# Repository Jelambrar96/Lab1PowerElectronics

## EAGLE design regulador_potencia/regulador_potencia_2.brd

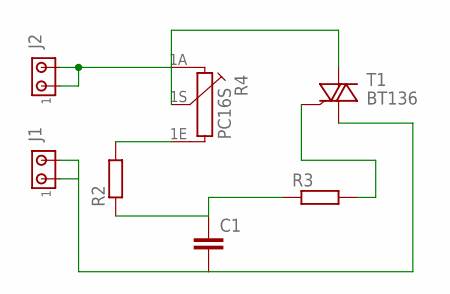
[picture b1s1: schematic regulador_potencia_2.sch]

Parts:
C1: C2.5/5; C2.5-5
J1, J2: MTA02-156; 1X2MTA
R2, R3: R-EU_0207/12; 0207/12
R4: PC16S
T1: BT136; TO220AB

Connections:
unnamed: R2.2, R4.1E
unnamed: J2.1, J2.2, R4.1A, R4.1S, T1.2 (A2)
unnamed: C1.2, J1.1, J1.2, T1.1 (A1)
unnamed: C1.1, R2.1, R3.1
unnamed: R3.2, T1.3 (G)

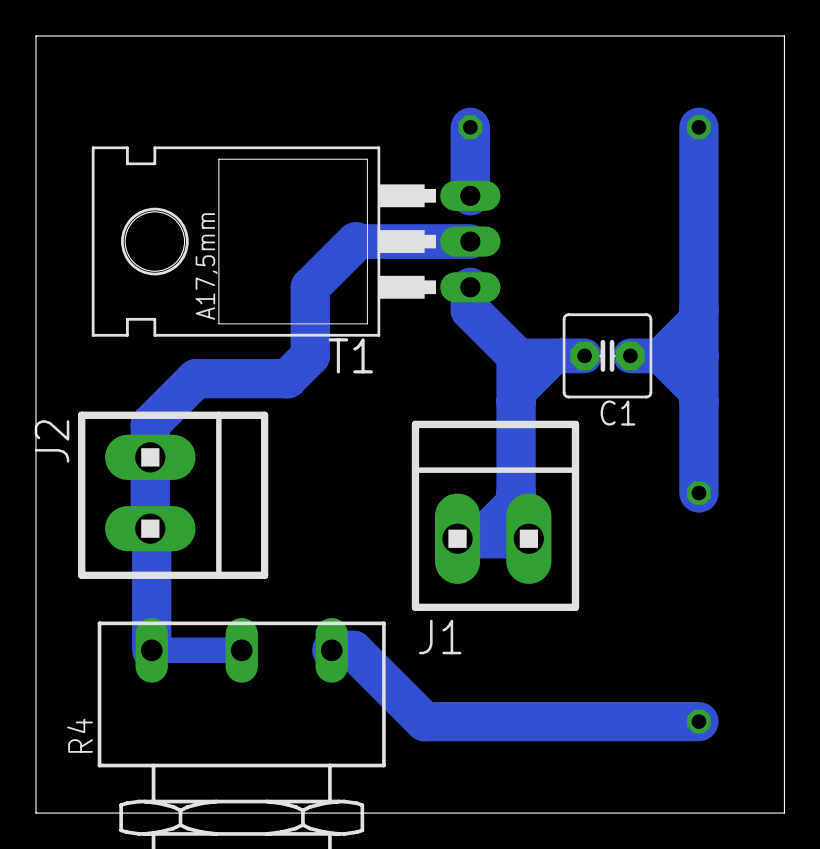
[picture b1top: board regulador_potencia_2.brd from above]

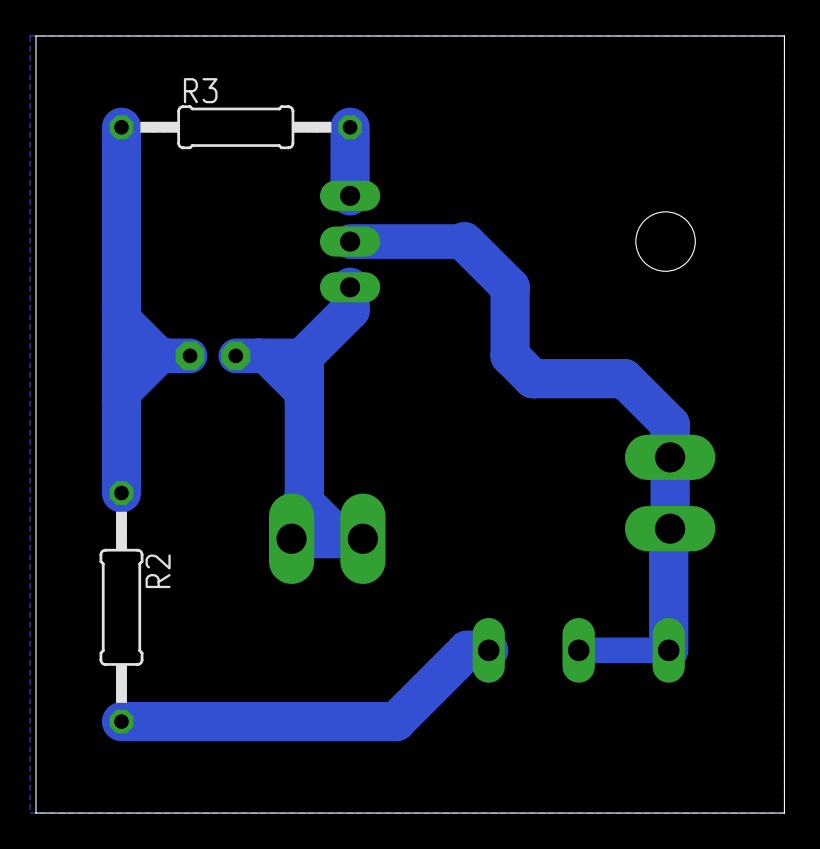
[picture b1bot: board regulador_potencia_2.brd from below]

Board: 2 copper layers, 41.6 x 43.2 mm, 7 parts (2 on the bottom side), 5 nets.

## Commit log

2018-03-08 commit2
2018-03-08 commit3
2018-03-08 commit4
2018-03-16 remove innesary files
2018-03-16 added controller mesarurements
2018-03-16 added instroduction
2018-03-17 change language document
2018-03-17 desing mwe code
2018-03-17 add new code
2018-03-17 add images folder
2018-03-17 add image folder
2018-03-17 add measure folder
2018-03-17 comit
2018-03-18 commti
2018-03-24 informe espanoñ
2018-03-25 final
2018-03-25 finaldoc
2020-01-20 add files to app tkinter
2020-03-06 fix error and change input, add requeriments.txt
